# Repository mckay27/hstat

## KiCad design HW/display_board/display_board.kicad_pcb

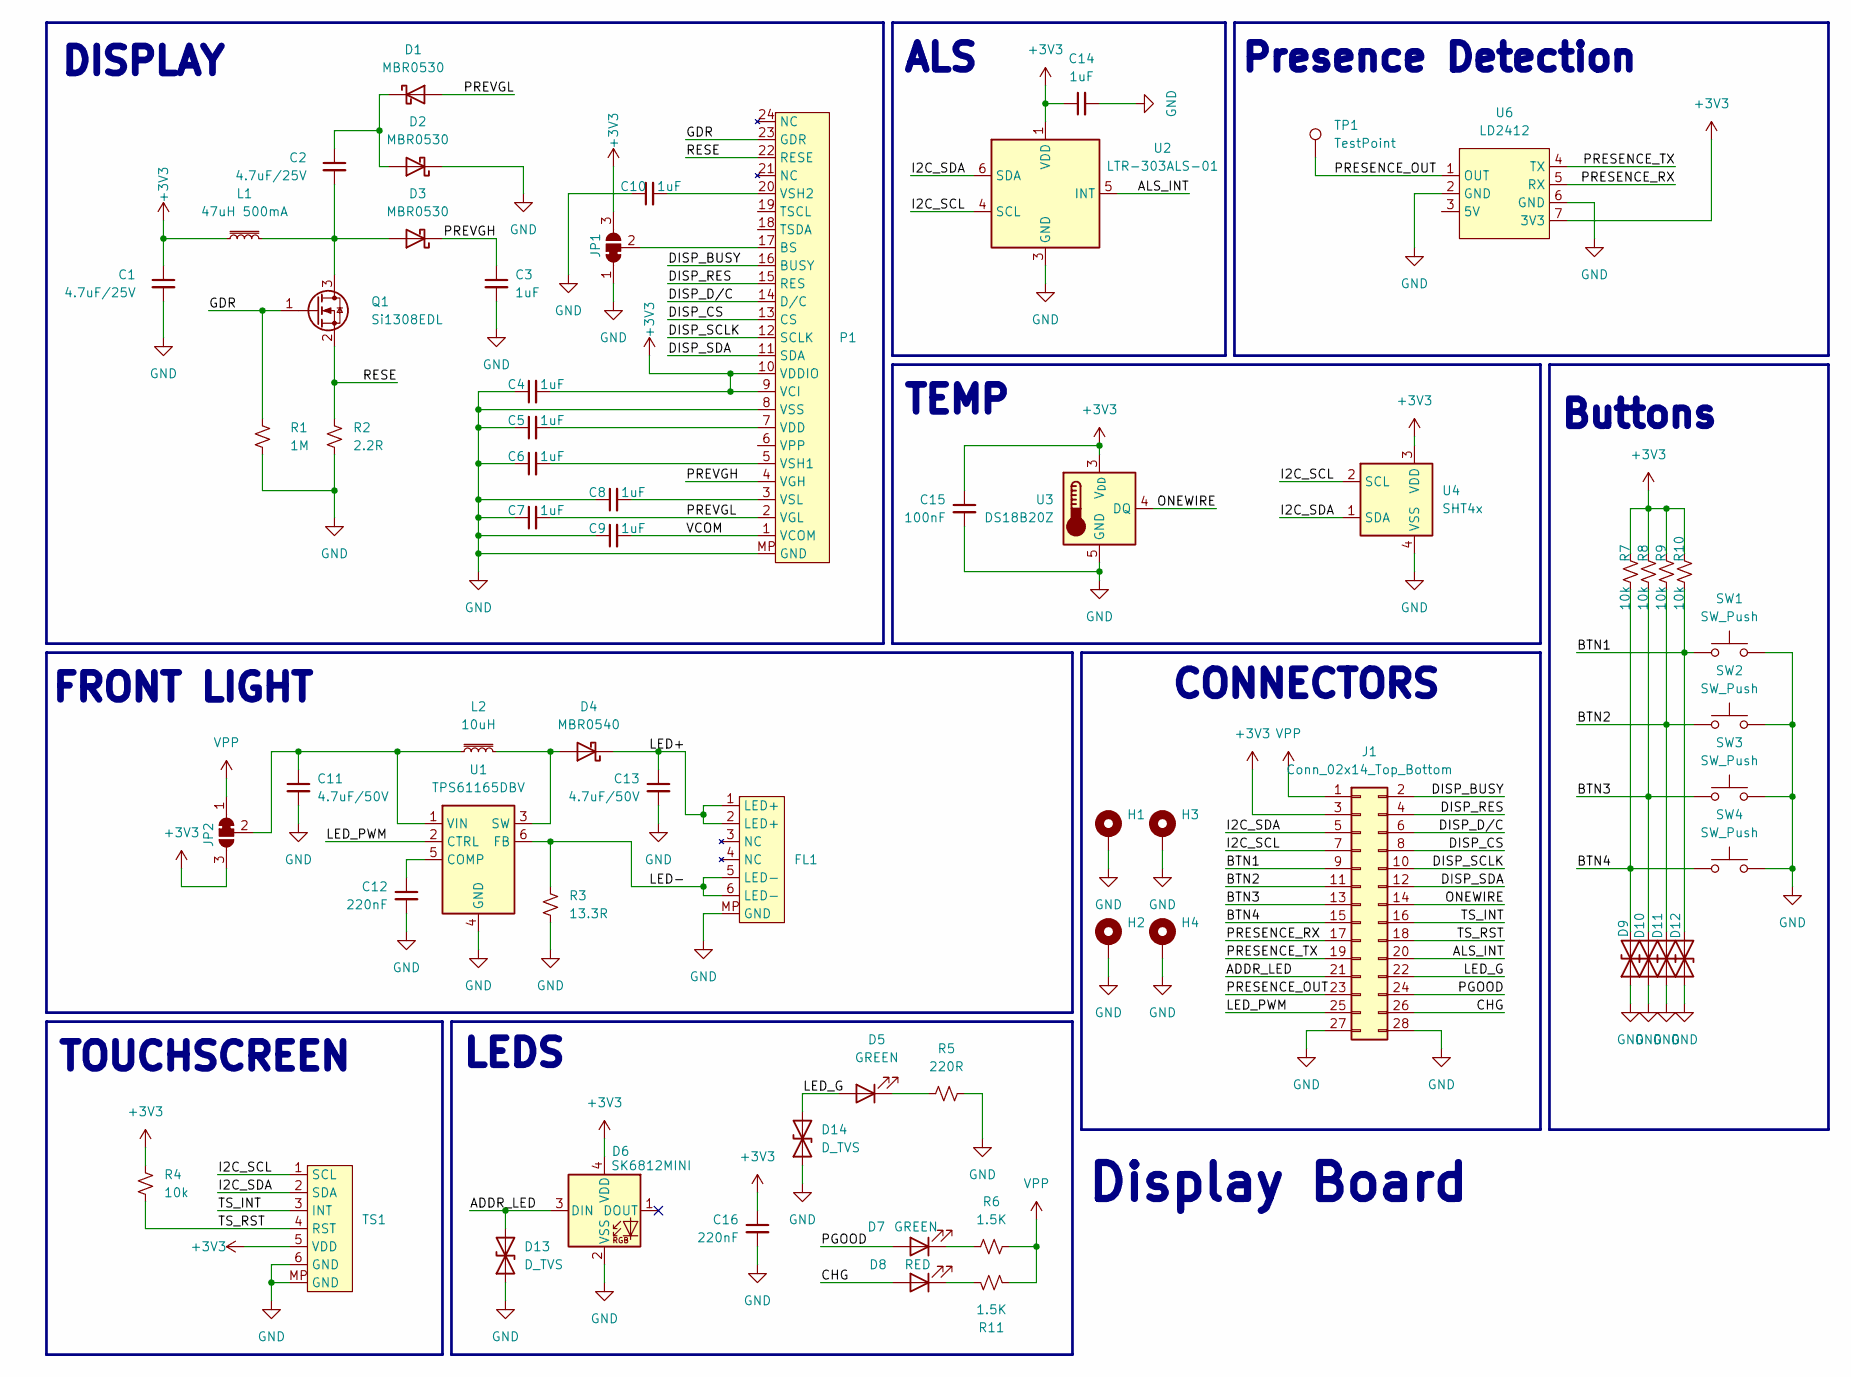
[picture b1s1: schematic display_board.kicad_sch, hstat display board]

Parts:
C1, C2: 4.7uF/25V; C_0603_1608Metric; PartsBox ID aw5pxnppqwhgq9d4hbptg59tfp
C3, C4, C5, C6, C7, C8, C9, C10, C14: 1uF; C_0603_1608Metric; PartsBox ID 6kadbs4vvekm59a2tdn2x98ymn
C11, C13: 4.7uF/50V; C_0805_2012Metric; PartsBox ID 7j02rd1hp8ghk8tj1z507f8pqg
C12, C16: 220nF; C_0603_1608Metric; PartsBox ID bsj51sepbckhc9y04nejax5532
C15: 100nF; C_0603_1608Metric; PartsBox ID 6afr1f2my2jjj8vs6v1p4rpr25
D1, D2, D3: MBR0530; D_SOD-123; MPN MBR0530-TP
D4: MBR0540; D_SOD-123; PartsBox ID 77578v3zwgkcma6xaqdbw1041c
D5, D7: GREEN; LED_0805_2012Metric; MPN KT-0805G
D6: SK6812MINI; LED_SK6812MINI_PLCC4_3.5x3.5mm_P1.75mm; MPN SK6812MINI-HS
D8: RED; LED_0805_2012Metric; MPN NCD0805R1
D9, D10, D11, D12, D13, D14: D_TVS; D_SOD-323; MPN H8VHD3B
FL1: AFC24-S06FIA-00
H1, H2, H3, H4: MountingHole_Pad; MountingHole_3.2mm_M3_ISO7380
J1: Conn_02x14_Top_Bottom; PinHeader_2x14_P2.54mm_Vertical_SMD
JP1, JP2: SolderJumper_3_Bridged12; SolderJumper-3_P1.3mm_Bridged12_RoundedPad1.0x1.5mm
L1: 47uH 500mA; L_Changjiang_FNR4012S; MPN FNR4012S470MT
L2: 10uH; L_Taiyo-Yuden_NR-40xx; MPN NRS4018T100MDGJ
P1: AFC24-S24FIA-00
Q1: Si1308EDL; SOT-323_SC-70; MPN SI1308EDL-T1-GE3
R1: 1M; R_0603_1608Metric; PartsBox ID 6jt3vpkk78jdvawzvaeg0wm6yf
R2: 2.2R; R_0603_1608Metric; PartsBox ID 8vn7xtt6zthxrb24xq1m7pnxd6
R3: 13.3R; R_0603_1608Metric; PartsBox ID 251d633bemhrbapgvqna90sr9j
R4, R7, R8, R9, R10: 10k; R_0603_1608Metric; PartsBox ID df49r6pnvckv7ajxacv2mbgt3r
R5: 220R; R_0603_1608Metric; PartsBox ID 1qgbwbrhs2jpe97grc235zphth
R6, R11: 1.5K; R_0603_1608Metric; PartsBox ID 8a565xcwbcjcr9p1vng5eaq7bh
SW1, SW2, SW3, SW4: SW_Push; SW_Push_1P1T_XKB_TS-1187A; MPN TS-1187A-B-A-B
TP1: TestPoint; TestPoint_Pad_2.0x2.0mm
TS1: AFC24-S06FIA-00
U1: TPS61165DBV; SOT-23-6; MPN TPS61165DBV
U2: LTR-303ALS-01; Lite-On_LTR-303ALS-01; MPN LTR-303ALS-01
U3: DS18B20Z; SOIC-8_3.9x4.9mm_P1.27mm; MPN DS18B20Z
U4: SHT4x; Sensirion_DFN-4_1.5x1.5mm_P0.8mm_SHT4x_NoCentralPad; MPN SHT41-AD1B-R2
U6: LD2412; MPN LD2412

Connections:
+3V3: C1.1, C4.2, C14.1, C15.1, C16.1, D6.4 (VDD), J1.3, JP1.3 (B), JP2.3 (B), L1.1, P1.9 (VCI), P1.10 (VDDIO), R4.1, R7.1, R8.1, R9.1, R10.1, TS1.5 (VDD), U2.1 (VDD), U3.3 (V_{DD}), U4.3 (VDD), U6.7 (3V3)
/ADDR_LED: D6.3 (DIN), D13.2 (A2), J1.21
/ALS_INT: J1.20, U2.5 (INT)
/BTN1: D12.2 (A2), J1.9, R10.2, SW1.1
/BTN2: D11.2 (A2), J1.11, R9.2, SW2.1
/BTN3: D10.2 (A2), J1.13, R8.2, SW3.1
/BTN4: D9.2 (A2), J1.15, R7.2, SW4.1
/CHG: D8.2 (A), J1.26
/DISP_BUSY: J1.2, P1.16 (BUSY)
/DISP_CS: J1.8, P1.13 (CS)
/DISP_D/C: J1.6, P1.14 (D/C)
/DISP_RES: J1.4, P1.15 (RES)
/DISP_SCLK: J1.10, P1.12 (SCLK)
/DISP_SDA: J1.12, P1.11 (SDA)
/GDR: P1.23 (GDR), Q1.1 (G), R1.1
/I2C_SCL: J1.7, TS1.1 (SCL), U2.4 (SCL), U4.2 (SCL)
/I2C_SDA: J1.5, TS1.2 (SDA), U2.6 (SDA), U4.1 (SDA)
/LED+: C13.1, D4.1 (K), FL1.1 (LED+), FL1.2 (LED+)
/LED-: FL1.5 (LED-), FL1.6 (LED-), R3.1, U1.6 (FB)
/LED_G: D5.2 (A), D14.2 (A2), J1.22
/LED_PWM: J1.25, U1.2 (CTRL)
/ONEWIRE: J1.14, U3.4 (DQ)
/PGOOD: D7.2 (A), J1.24
/PRESENCE_OUT: J1.23, TP1.1, U6.1 (OUT)
/PRESENCE_RX: J1.17, U6.5 (RX)
/PRESENCE_TX: J1.19, U6.4 (TX)
/PREVGH: C3.1, D3.1 (K), P1.4 (VGH)
/PREVGL: C7.2, D1.2 (A), P1.2 (VGL)
/RESE: P1.22 (RESE), Q1.2 (S), R2.1
/TS_INT: J1.16, TS1.3 (INT)
/TS_RST: J1.18, R4.2, TS1.4 (RST)
/VCOM: C9.2, P1.1 (VCOM)
GND: C1.2, C3.2, C4.1, C5.1, C6.1, C7.1, C8.1, C9.1, C10.1, C11.2, C12.2, C13.2, C14.2, C15.2, C16.2, D2.1 (K), D6.2 (VSS), D9.1 (A1), D10.1 (A1), D11.1 (A1), D12.1 (A1), D13.1 (A1), D14.1 (A1), FL1.MP (GND), H1.1, H2.1, H3.1, H4.1, J1.27, J1.28, JP1.1 (A), P1.8 (VSS), P1.MP (GND), R1.2, R2.2, R3.2, R5.2, SW1.2, SW2.2, SW3.2, SW4.2, TS1.6 (GND), TS1.MP (GND), U1.4 (GND), U2.3 (GND), U3.5 (GND), U4.4 (VSS), U6.2 (GND), U6.6 (GND)
unnamed: C2.1, D1.1 (K), D2.2 (A)
unnamed: C2.2, D3.2 (A), L1.2, Q1.3 (D)
unnamed: D4.2 (A), L2.2, U1.3 (SW)
unnamed: D5.1 (K), R5.1
unnamed: D7.1 (K), R6.2
unnamed: D8.1 (K), R11.1
unnamed: JP1.2 (C), P1.17 (BS)
unnamed: C11.1, JP2.2 (C), L2.1, U1.1 (VIN)
unnamed: C5.2, P1.7 (VDD)
unnamed: C6.2, P1.5 (VSH1)
unnamed: C10.2, P1.20 (VSH2)
unnamed: C8.2, P1.3 (VSL)
unnamed: C12.1, U1.5 (COMP)
VPP: J1.1, JP2.1 (A), R6.1, R11.2

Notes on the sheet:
DISPLAY
Presence Detection
TEMP
Display Board
LEDS
CONNECTORS
Buttons
TOUCHSCREEN
ALS
FRONT LIGHT

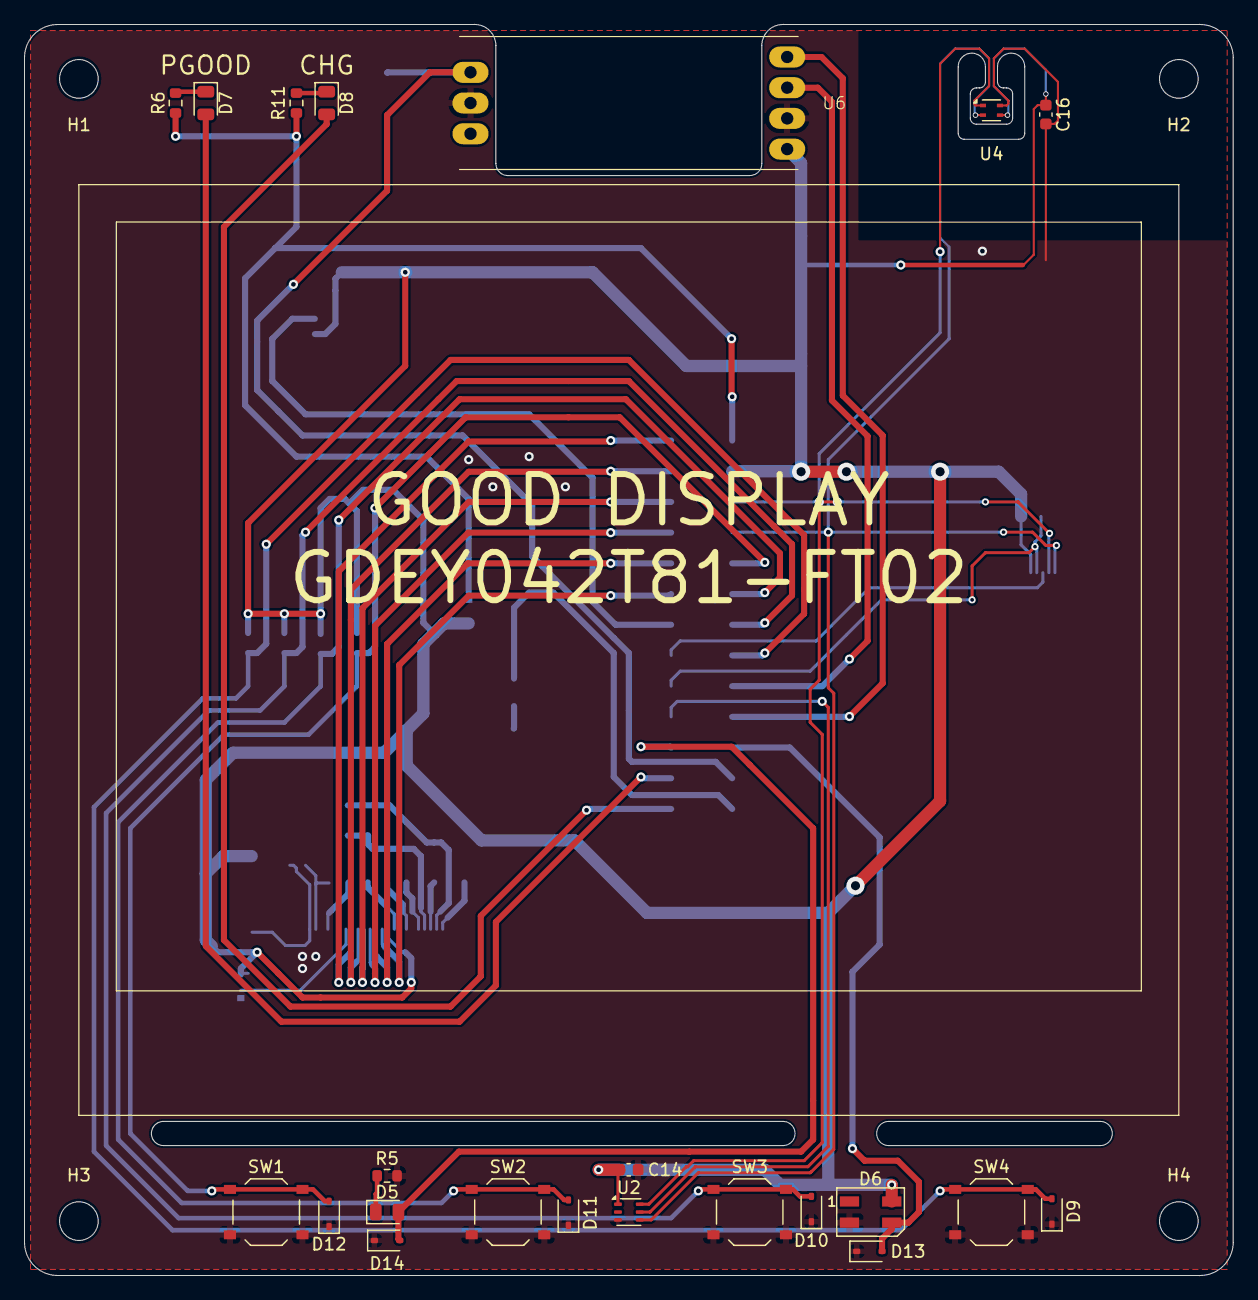
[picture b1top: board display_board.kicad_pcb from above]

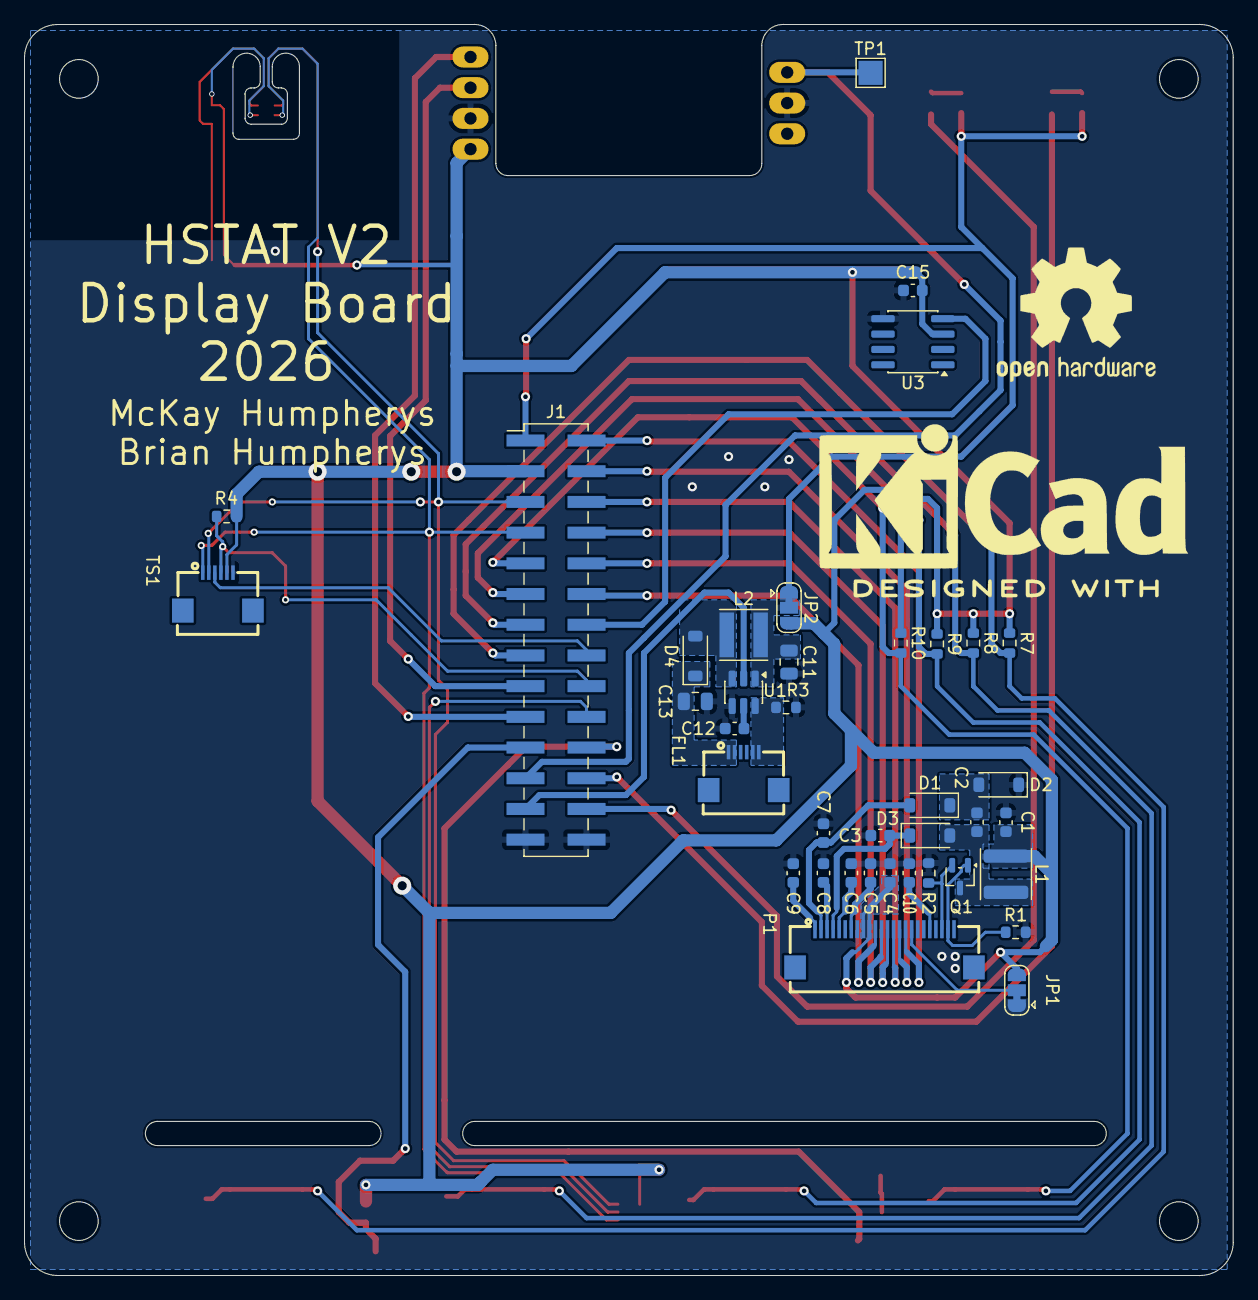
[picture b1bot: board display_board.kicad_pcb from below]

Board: 2 copper layers, 100.0 x 103.5 mm, 64 parts (38 on the bottom side), 47 nets.

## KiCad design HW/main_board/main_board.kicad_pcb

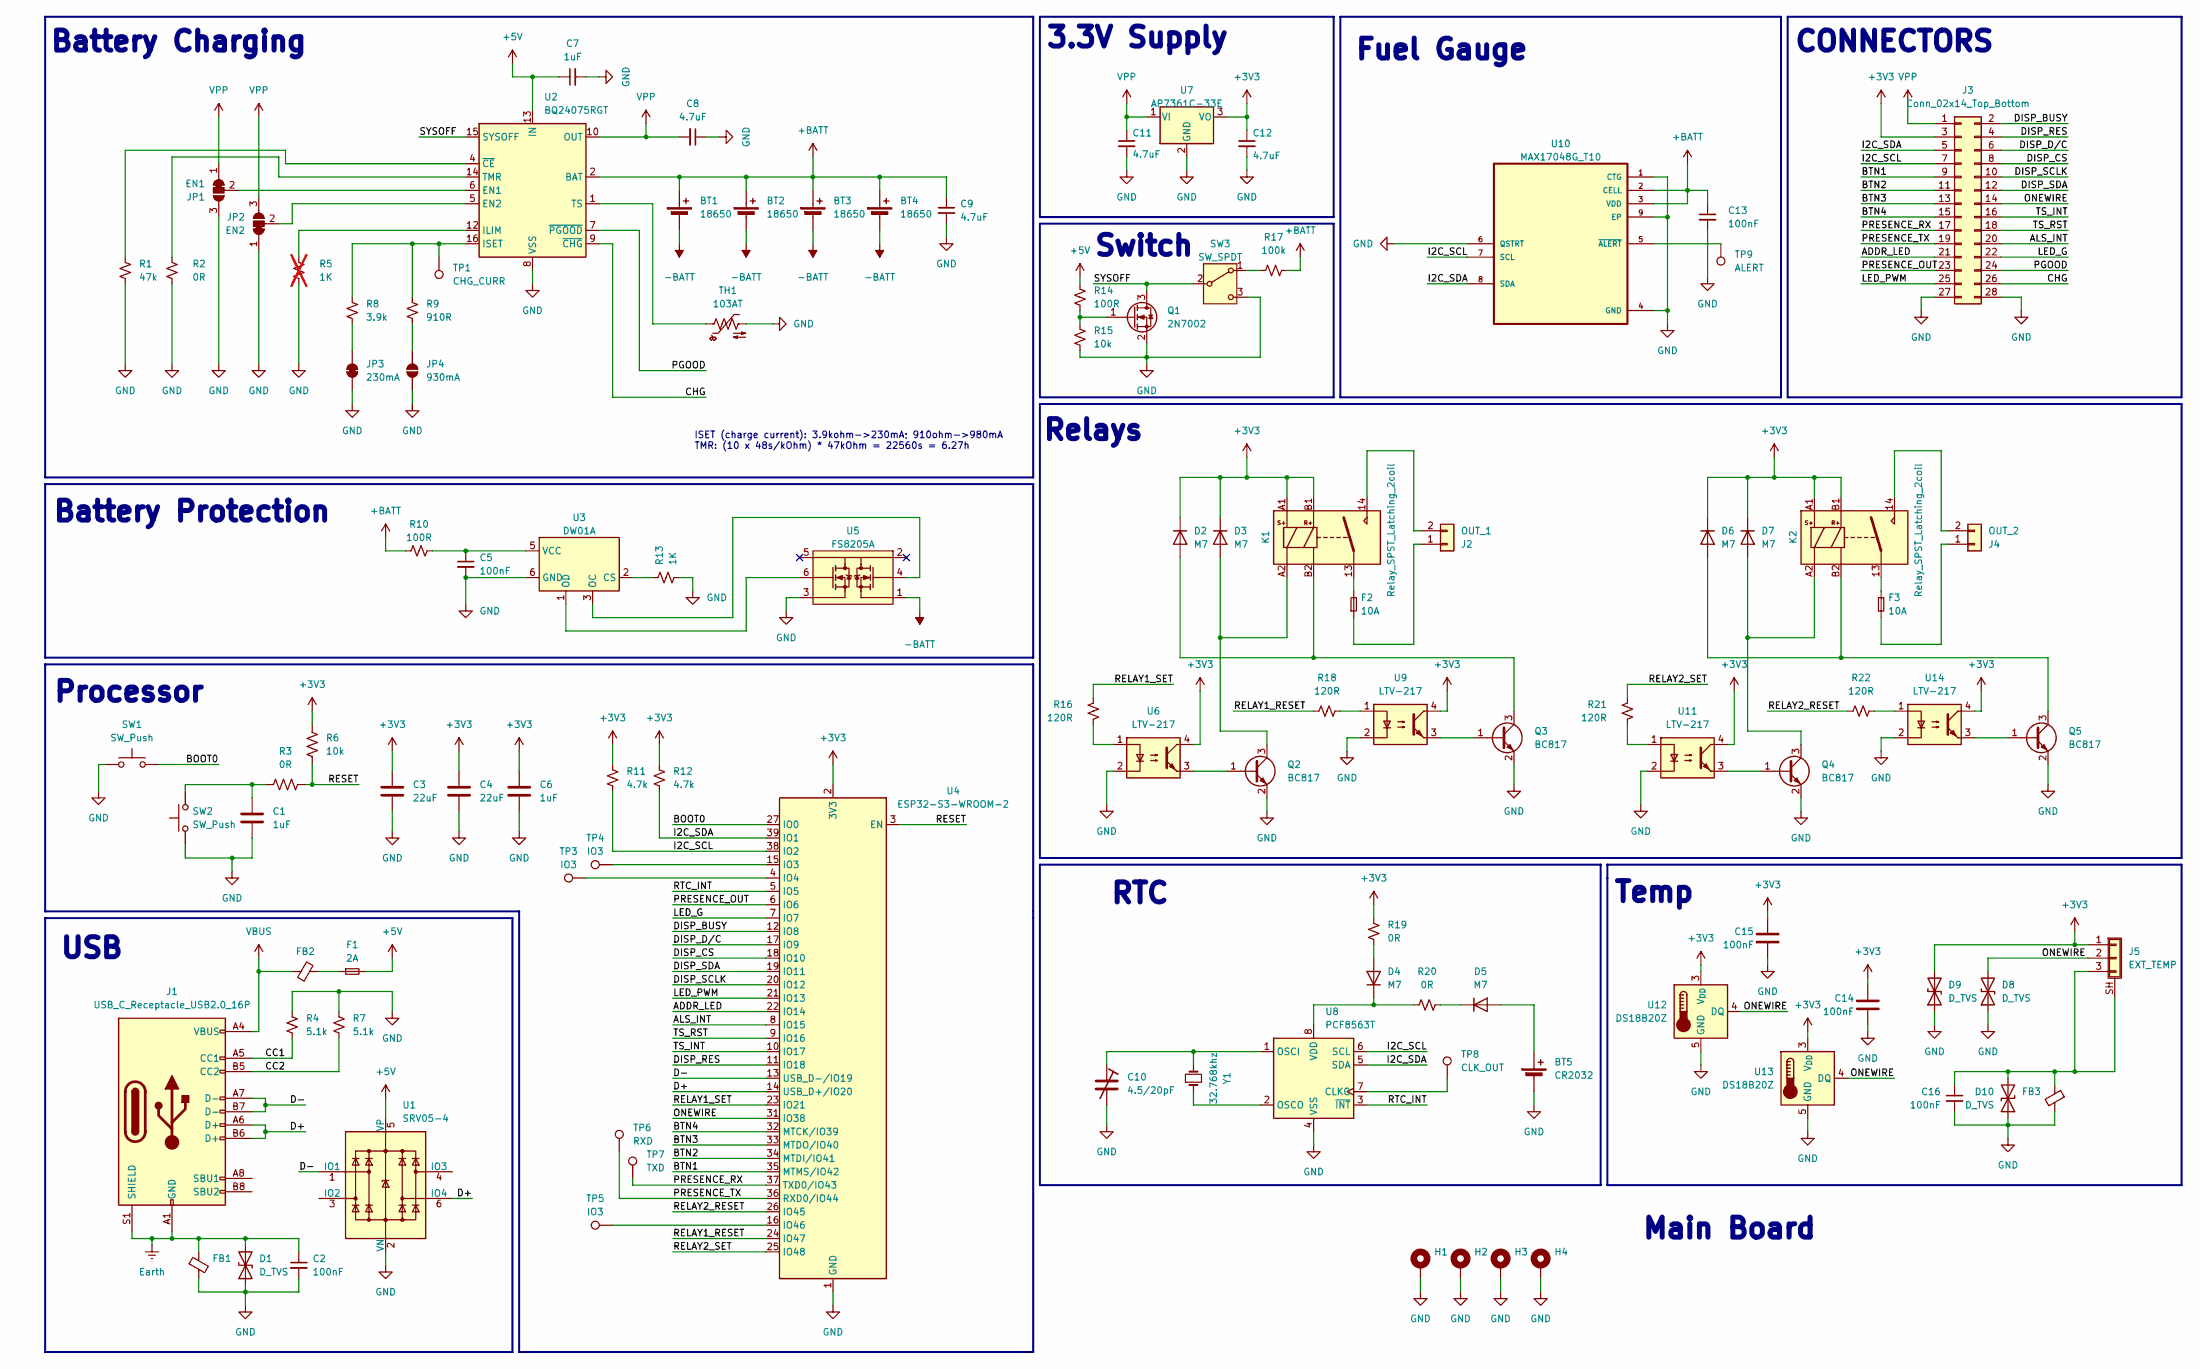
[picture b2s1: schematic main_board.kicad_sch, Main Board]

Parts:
BT1, BT2, BT3, BT4: 18650; 1043-keystone-18650; MPN 1043
BT5: CR2032; BatteryHolder_Keystone_1058_1x2032; MPN 1058
C1, C6, C7: 1uF; C_0603_1608Metric; PartsBox ID 6kadbs4vvekm59a2tdn2x98ymn
C2, C5, C13, C14, C15, C16: 100nF; C_0603_1608Metric; PartsBox ID 6afr1f2my2jjj8vs6v1p4rpr25
C3, C4: 22uF; C_0603_1608Metric; PartsBox ID 11f9t6q8q6hhk8b1pmjvgccz5x
C8, C9, C11, C12: 4.7uF; C_0603_1608Metric; PartsBox ID aw5pxnppqwhgq9d4hbptg59tfp
C10: 4.5/20pF; C_Trimmer_Voltronics_JZ; MPN JZ200HV
D1, D8, D9, D10: D_TVS; D_SOD-323; MPN H8VHD3B
D2, D3, D4, D5, D6, D7: M7; D_SMA; PartsBox ID 3vcxfjzjhpj7690trekrvkgr7w
F1: 2A; Fuse_1206_3216Metric_Pad1.42x1.75mm_HandSolder
F2, F3: 10A; Fuseholder_Clip-5x20mm_Littelfuse_111_Lateral_P18.80x5.00mm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; MPN 01110501Z
FB1, FB2, FB3: FerriteBead_Small; L_0603_1608Metric; MPN BLM18PG121SN1D
H1, H2, H3, H4: MountingHole_Pad; MountingHole_3.2mm_M3_ISO7380
J1: USB_C_Receptacle_USB2.0_16P; USB_C_Receptacle_G-Switch_GT-USB-7010ASV; MPN GT-USB-7010ASV
J2: OUT_1; CONN2_2604-1102_WAG; MPN 2604-1102
J3: Conn_02x14_Top_Bottom; PinSocket_2x14_P2.54mm_Vertical_SMD
J4: OUT_2; CONN2_2604-1102_WAG; MPN 2604-1102
J5: EXT_TEMP; PHOENIX_1771033; MPN 1771033
JP1: EN1; SolderJumper-3_P1.3mm_Bridged12_RoundedPad1.0x1.5mm
JP2: EN2; SolderJumper-3_P1.3mm_Bridged12_RoundedPad1.0x1.5mm
JP3: 230mA; SolderJumper-2_P1.3mm_Bridged_RoundedPad1.0x1.5mm
JP4: 930mA; SolderJumper-2_P1.3mm_Open_RoundedPad1.0x1.5mm
K1, K2: Relay_SPST_Latching_2coil; RELAY_G6CK-1117P-US_OMR; MPN G6CK-1117P-US-DC3
Q1: 2N7002; SOT-23; MPN 2N7002
Q2, Q3, Q4, Q5: BC817; SOT-23; MPN BC817-40
R1: 47k; R_0603_1608Metric; PartsBox ID 1aemmt28hmjbp9y1k30rczecpr
R2, R3, R19, R20: 0R; R_0603_1608Metric; PartsBox ID 8qd6rd2jk8jw398ybjyyrmq1tq
R4, R7: 5.1k; R_0603_1608Metric; PartsBox ID 9ecv7q3vv2knm8vest68b07d9j
R5: 1K; R_0603_1608Metric; PartsBox ID e64yh28w3ej2mbe5sh0xf25qpt; not fitted
R6, R15: 10k; R_0603_1608Metric; PartsBox ID df49r6pnvckv7ajxacv2mbgt3r
R8: 3.9k; R_0603_1608Metric; PartsBox ID 5v44h5wt9ck18a2815smpxngts
R9: 910R; R_0603_1608Metric; PartsBox ID efjv3egq1rhyg8vvdsvfw39abg
R10, R14: 100R; R_0603_1608Metric; PartsBox ID dqk7283n2thpca2y9nhycmgdpt
R11, R12: 4.7k; R_0603_1608Metric; PartsBox ID cb7fy4f2b2jq09t4n4p298ayaa
R13: 1K; R_0603_1608Metric; PartsBox ID e64yh28w3ej2mbe5sh0xf25qpt
R16, R18, R21, R22: 120R; R_0603_1608Metric; PartsBox ID 6kyk5zk2zegvt8f9vh34bzh7ka
R17: 100k; R_0603_1608Metric; PartsBox ID ad7wkgw7d2hthbb72xtkfgq7rp
SW1, SW2: SW_Push; SW_Push_1P1T_XKB_TS-1187A; MPN TS-1187A-B-A-B
SW3: SW_SPDT; SW_E-Switch_EG1224_SPDT_Angled; MPN EG1224
TH1: 103AT; R_0603_1608Metric; MPN B57332V5103F360
TP1: CHG_CURR; TestPoint_Pad_2.0x2.0mm
TP3, TP4, TP5: IO3; TestPoint_Pad_2.0x2.0mm
TP6: RXD; TestPoint_Pad_2.0x2.0mm
TP7: TXD; TestPoint_Pad_2.0x2.0mm
TP8: CLK_OUT; TestPoint_Loop_D2.54mm_Drill1.5mm_Beaded
TP9: ALERT; TestPoint_Pad_2.0x2.0mm
U1: SRV05-4; SOT-23-6; MPN SRV05-4-P-T7
U2: BQ24075RGT; VQFN-16-1EP_3x3mm_P0.5mm_EP1.6x1.6mm; MPN BQ24075TRGTR
U3: DW01A; SOT-23-6; MPN DW01A
U4: ESP32-S3-WROOM-2; MPN ESP32-S3-WROOM-2-N32R16V
U5: FS8205A; SOT-23-6; MPN FS8205A
U6, U9, U11, U14: LTV-217; SOP-4_4.4x2.6mm_P1.27mm; MPN LTV-217-B-G
U7: AP7361C-33E; SOT-223-3_TabPin2; MPN AP7361C-33E-13
U8: PCF8563T; SOIC-8_3.9x4.9mm_P1.27mm; MPN PCF8563T/5,518
U10: MAX17048G_T10; SON50P200X200X80-9N; MPN MAX17048G+T10
U12, U13: DS18B20Z; SOIC-8_3.9x4.9mm_P1.27mm; MPN DS18B20Z
Y1: 32.768khz; Crystal_SMD_3215-2Pin_3.2x1.5mm; MPN Q13FC13500004

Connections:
+5V: C7.1, F1.2, R14.1, U1.5 (VP), U2.13 (IN)
+BATT: BT1.1 (+), BT2.1 (+), BT3.1 (+), BT4.1 (+), C9.1, C13.1, R10.1, R17.2, U2.2 (BAT), U2.3 (BAT), U10.2 (CELL), U10.3 (VDD)
-BATT: BT1.2 (-), BT2.2 (-), BT3.2 (-), BT4.2 (-), U5.1 (S1)
/ADDR_LED: J3.21, U4.22 (IO14)
/ALS_INT: J3.20, U4.8 (IO15)
/BOOT0: SW1.2, U4.27 (IO0)
/BTN1: J3.9, U4.35 (MTMS/IO42)
/BTN2: J3.11, U4.34 (MTDI/IO41)
/BTN3: J3.13, U4.33 (MTDO/IO40)
/BTN4: J3.15, U4.32 (MTCK/IO39)
/CC1: J1.A5 (CC1), R4.2
/CC2: J1.B5 (CC2), R7.2
/CHG: J3.26, U2.9 (~CHG)
/D+: J1.A6 (D+), J1.B6 (D+), U1.6 (IO4), U4.14 (USB_D+/IO20)
/D-: J1.A7 (D-), J1.B7 (D-), U1.1 (IO1), U4.13 (USB_D-/IO19)
/DISP_BUSY: J3.2, U4.12 (IO8)
/DISP_CS: J3.8, U4.18 (IO10)
/DISP_D/C: J3.6, U4.17 (IO9)
/DISP_RES: J3.4, U4.11 (IO18)
/DISP_SCLK: J3.10, U4.20 (IO12)
/DISP_SDA: J3.12, U4.19 (IO11)
/I2C_SCL: J3.7, R11.2, U4.38 (IO2), U8.6 (SCL), U10.7 (SCL)
/I2C_SDA: J3.5, R12.2, U4.39 (IO1), U8.5 (SDA), U10.8 (SDA)
/LED_G: J3.22, U4.7 (IO7)
/LED_PWM: J3.25, U4.21 (IO13)
/ONEWIRE: D8.2 (A2), J3.14, J5.2, U4.31 (IO38), U12.4 (DQ), U13.4 (DQ)
/PGOOD: J3.24, U2.7 (~PGOOD)
/PRESENCE_OUT: J3.23, U4.6 (IO6)
/PRESENCE_RX: J3.17, TP7.1, U4.37 (TXD0/IO43)
/PRESENCE_TX: J3.19, TP6.1, U4.36 (RXD0/IO44)
/RELAY1_RESET: R18.1, U4.24 (IO47)
/RELAY1_SET: R16.1, U4.23 (IO21)
/RELAY2_RESET: R22.1, U4.26 (IO45)
/RELAY2_SET: R21.1, U4.25 (IO48)
/RESET: R3.2, R6.2, U4.3 (EN)
/RTC_INT: U4.5 (IO5), U8.3 (~INT)
/SYSOFF: Q1.3 (D), SW3.2 (B), U2.15 (SYSOFF)
/TS_INT: J3.16, U4.10 (IO17)
/TS_RST: J3.18, U4.9 (IO16)
Earth: C2.1, D1.2 (A2), FB1.1, J1.A1 (GND), J1.A12 (GND), J1.B1 (GND), J1.B12 (GND), J1.S1 (SHIELD)
unnamed: BT5.1 (+), D5.2 (A)
unnamed: C1.1, R3.1, SW2.2
unnamed: D2.2 (A), K1.B2, Q3.3 (C)
unnamed: D3.2 (A), K1.A2, Q2.3 (C)
unnamed: D4.2 (A), R19.1
unnamed: D4.1 (K), R20.1, U8.8 (VDD)
unnamed: D5.1 (K), R20.2
unnamed: D6.2 (A), K2.B2, Q5.3 (C)
unnamed: D7.2 (A), K2.A2, Q4.3 (C)
unnamed: C16.1, D10.2 (A2), FB3.1, J5.3, J5.SH (Shield)
unnamed: F1.1, FB2.2
unnamed: F2.2, K1.13
unnamed: F3.2, K2.13
unnamed: F2.1, J2.1
unnamed: J2.2, K1.14
unnamed: F3.1, J4.1
unnamed: J4.2, K2.14
unnamed: JP1.2 (C), U2.6 (EN1)
unnamed: JP2.2 (C), U2.5 (EN2)
unnamed: JP3.2 (B), R8.2
unnamed: JP4.2 (B), R9.2
unnamed: Q1.1 (G), R14.2, R15.1
unnamed: Q2.1 (B), U6.3
unnamed: Q3.1 (B), U9.3
unnamed: Q4.1 (B), U11.3
unnamed: Q5.1 (B), U14.3
unnamed: R16.2, U6.1
unnamed: R18.2, U9.1
unnamed: R21.2, U11.1
unnamed: R22.2, U14.1
unnamed: R17.1, SW3.1 (A)
unnamed: R5.1, U2.12 (ILIM)
unnamed: R8.1, R9.1, TP1.1, U2.16 (ISET)
unnamed: R2.1, U2.14 (TMR)
unnamed: TH1.1, U2.1 (TS)
unnamed: R1.1, U2.4 (~CE)
unnamed: R13.1, U3.2 (CS)
unnamed: U3.3 (OC), U5.4 (G1)
unnamed: U3.1 (OD), U5.6 (G2)
unnamed: C5.1, R10.2, U3.5 (VCC)
unnamed: TP4.1, U4.15 (IO3)
unnamed: TP3.1, U4.4 (IO4)
unnamed: TP5.1, U4.16 (IO46)
unnamed: TP8.1, U8.7 (CLKO)
unnamed: C10.1, U8.1 (OSCI), Y1.2
unnamed: U8.2 (OSCO), Y1.1
unnamed: TP9.1, U10.5 (~ALERT)
VBUS: FB2.1, J1.A4 (VBUS), J1.A9 (VBUS), J1.B4 (VBUS), J1.B9 (VBUS)
VPP: C8.2, C11.1, J3.1, JP1.1 (A), JP2.3 (B), U2.10 (OUT), U2.11 (OUT), U7.1 (VI)

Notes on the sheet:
USB
Temp
Processor
Main Board
Fuel Gauge
Relays
Battery Charging
Battery Protection
CONNECTORS
RTC
Switch
3.3V Supply
ISET (charge current): 3.9kohm->230mA; 910ohm->980mA TMR: (10 x 48s/kOhm) * 47kOhm = 22560s = 6.27h

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
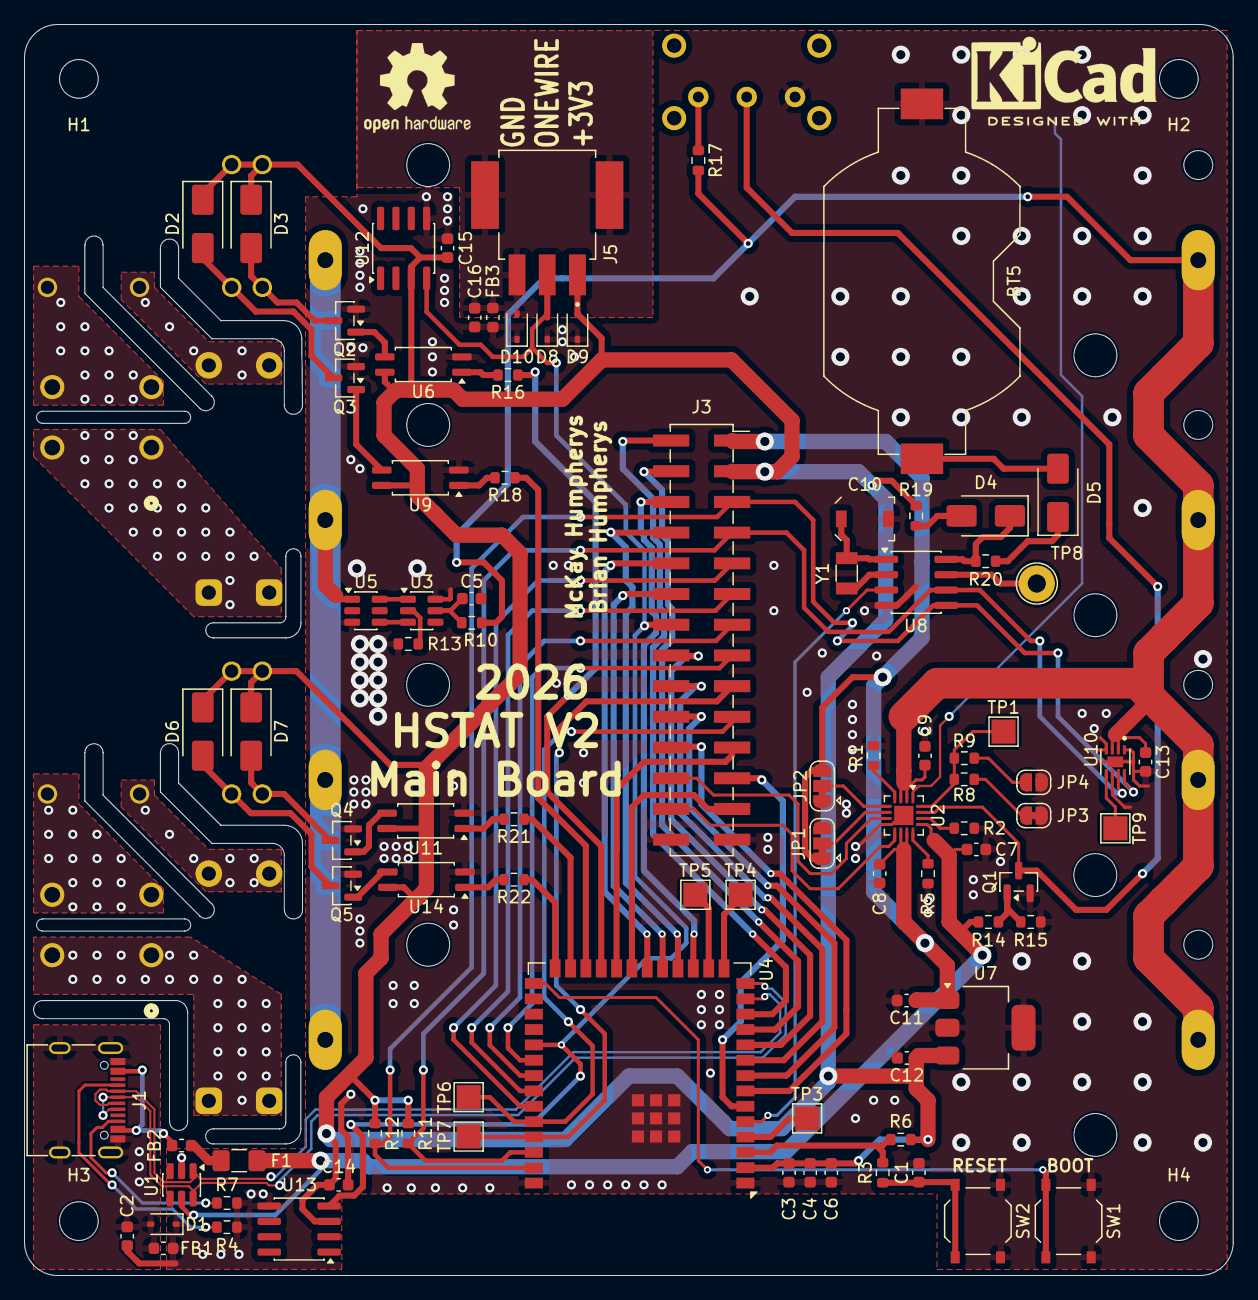
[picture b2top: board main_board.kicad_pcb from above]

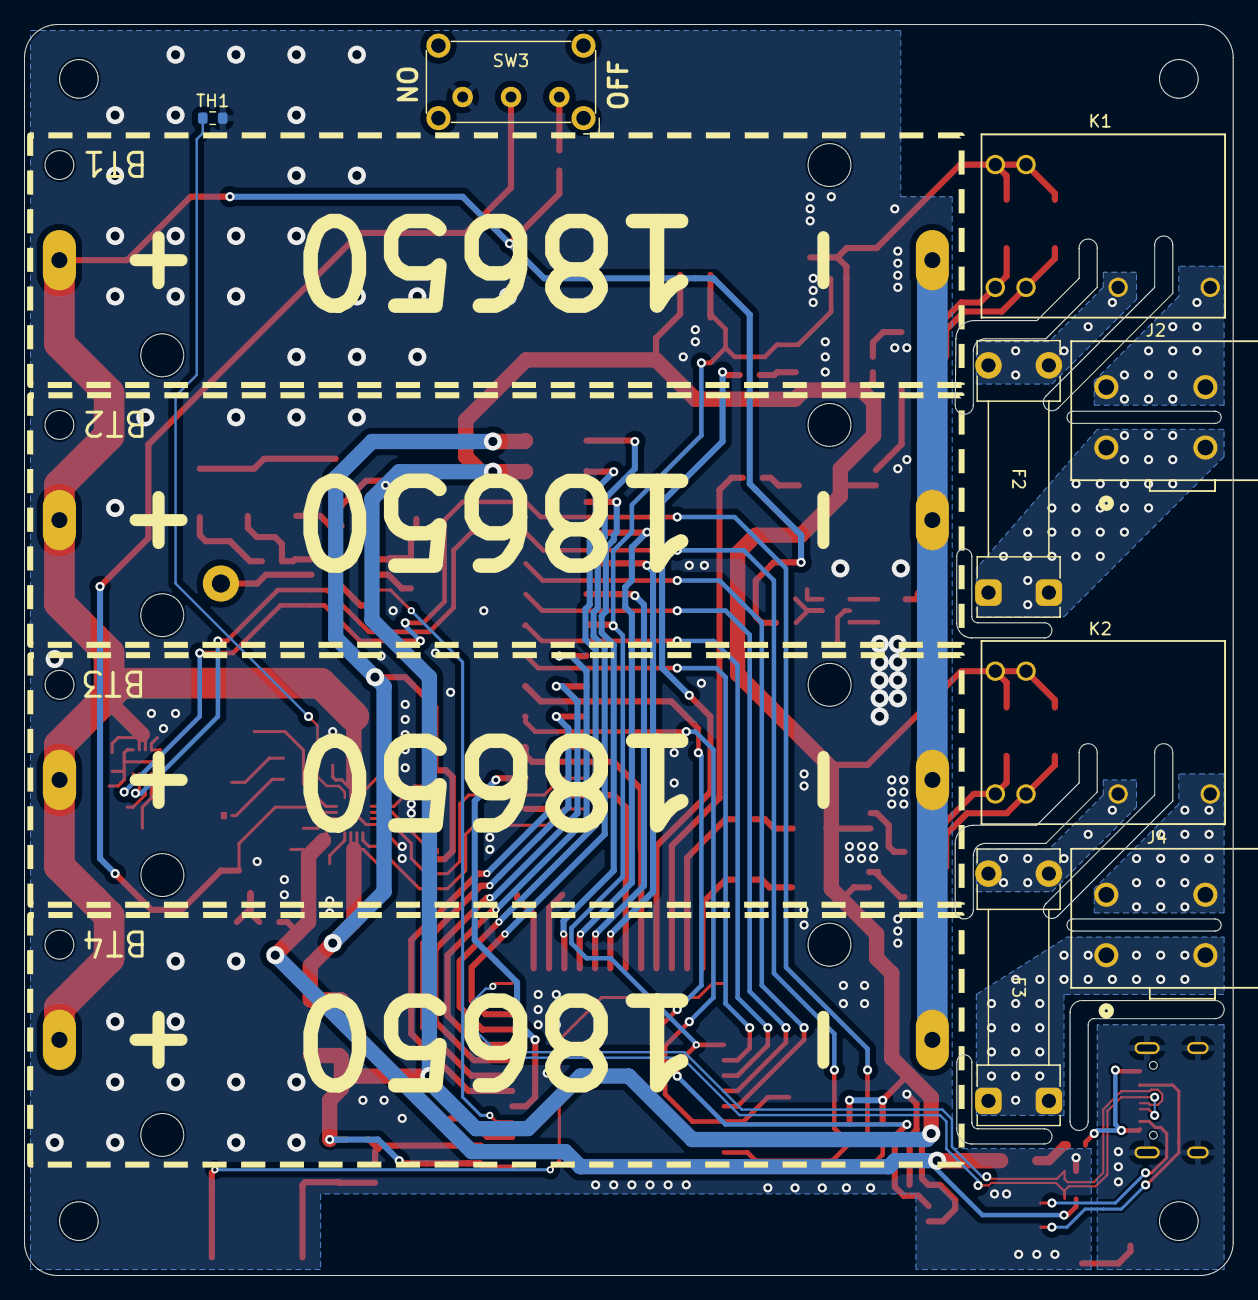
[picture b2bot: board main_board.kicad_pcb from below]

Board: 2 copper layers, 100.0 x 103.5 mm, 106 parts (12 on the bottom side), 91 nets.

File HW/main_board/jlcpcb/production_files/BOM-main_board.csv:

Comment,Designator,Footprint,LCSC,Quantity
0R,"R19,R2,R20,R3",R_0603_1608Metric,C21189,4
100R,"R10,R14",R_0603_1608Metric,C22775,2
100k,R17,R_0603_1608Metric,C25803,1
100nF,"C13,C14,C15,C16,C2,C5",C_0603_1608Metric,C14663,6
10k,"R15,R6",R_0603_1608Metric,C25804,2
120R,"R16,R18,R21,R22",R_0603_1608Metric,C22787,4
1K,R13,R_0603_1608Metric,C21190,1
1uF,"C1,C6,C7",C_0603_1608Metric,C15849,3
22uF,"C3,C4",C_0603_1608Metric,C59461,2
2N7002,Q1,SOT-23,C8545,1
3.9k,R8,R_0603_1608Metric,C23018,1
32.768khz,Y1,Crystal_SMD_3215-2Pin_3.2x1.5mm,C32346,1
4.7k,"R11,R12",R_0603_1608Metric,C23162,2
4.7uF,"C11,C12,C8,C9",C_0603_1608Metric,C19666,4
47k,R1,R_0603_1608Metric,C25819,1
5.1k,"R4,R7",R_0603_1608Metric,C23186,2
BC817,"Q2,Q3,Q4,Q5",SOT-23,C20069155,4
BQ24075RGT,U2,VQFN-16-1EP_3x3mm_P0.5mm_EP1.6x1.6mm,C2865459,1
D_TVS,"D1,D10,D8,D9",D_SOD-323,C20615808,4
FerriteBead_Small,"FB1,FB2,FB3",L_0603_1608Metric,C14709,3
LTV-217,"U11,U14,U6,U9",SOP-4_4.4x2.6mm_P1.27mm,C115450,4
M7,"D2,D3,D4,D5,D6,D7",D_SMA,C95872,6
MAX17048G_T10,U10,SON50P200X200X80-9N,C2682616,1
PCF8563T,U8,SOIC-8_3.9x4.9mm_P1.27mm,C7440,1
SRV05-4,U1,SOT-23-6,C85364,1
SW_Push,"SW1,SW2",SW_Push_1P1T_XKB_TS-1187A,C318884,2
IO3,TP4,TestPoint_Pad_2.0x2.0mm,,1
IO3,TP3,TestPoint_Pad_2.0x2.0mm,,1
IO3,TP5,TestPoint_Pad_2.0x2.0mm,,1
ALERT,TP9,TestPoint_Pad_2.0x2.0mm,,1
CHG_CURR,TP1,TestPoint_Pad_2.0x2.0mm,,1
4.5/20pF,C10,C_Trimmer_Voltronics_JZ,,1
RXD,TP6,TestPoint_Pad_2.0x2.0mm,,1
TXD,TP7,TestPoint_Pad_2.0x2.0mm,,1
CR2032,BT5,BatteryHolder_Keystone_1058_1x2032,,1
